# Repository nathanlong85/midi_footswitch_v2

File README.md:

# MIDI Footswitch v2

## The General Idea

The idea behind this is to be a customizable, solid footswitch for sending and receiving MIDI commands via USB. The following buttons will be implemented:

| Button | Count | Function |
|--------|-------|----------|
| MIDI PC  | 5 | Send a Program Change MIDI command to switch between presets, snapshots, etc. |
| MIDI CC  | 6 | Send a Control Change MIDI command to switch pedals on/off |
| PC StepDown | 1 | Lower the range of PC numbers corresponding with the buttons (e.g. 6-10 to 1-5) |
| PC StepUp | 1 | Raise the range of PC numbers corresponding with the buttons (e.g. 1-5 to 6-10) |
| TempoTap | 1 | This'll probably just end up being a CC button |

The main purpose of this footswitch is to control guitar plugins and presets, specifically in LiveProfessor, but the MIDI out features should all still work fine in another program. Additionally, the footswitch accepts MIDI input. This allows LiveProfessor to send (for example) CC commands when switching presets that will control the button states and have them match up with the plugin states in the preset.

For example, if I switch to a preset that has only a TS808 plugin enabled, the footswitch will first switch all CC buttons off. Then LiveProfessor can send a CC command back to the footswitch to let it know that the button that corresponds with the TS808 should be on.

## Components Used

| Type | Count | Brand | Model | Link | Notes |
|------|-------|-------|------|-------|-------|
| Arduino | 1 | Elegoo | Mega2560 | | Chosen for the large number of pins available for buttons |
| Connections Board | 1 | Custom | N/A | N/A | Mostly a convenience to make things as modular as possible. Also used in place of a breadboard for components such as resistors for the LEDs and switches |
| Display | 1 | Teyleten Robot | 2.42" 128x64 SSD1309 OLED | https://a.co/d/j11dIGv | Connected via SPI |
| LED | 14 | N/A | N/A | N/A | Red 5mm |
| LED Holder | 14 | DaierTek | 5MM LED Lamp Holder | https://a.co/d/9saOy9M | |
| SD Card Module | 1 | HiLetgo | Micro SD TF Card Adater Reader Module | https://a.co/d/amf9kn3 | Connected via SPI |
| SD Card | 1 | | | | No need for a high capacity as the only things being stored are configs |
| FootSwitch | 14 | ESUPPORT | Momentary SPST Button | https://a.co/d/4z8qo4Z | |
| TSR Jack | 1 | Kingsing | N/A | https://a.co/d/iaOluce | For the expression pedal |
| Switch | 1 | uxcell | SS12F32-G7 | https://a.co/d/9ZpxkgF | Mini slider switch to change USB modes from Midi to Arduino for uploads |
| USB Jack | 1 | QIANRENON | N/A | https://a.co/d/0RwaqkX | USB-A to USB-C converter and passthrough plate |

Additionally, various electrical components, connector wires, header pins, etc. were used. Those should be available in the KiCad schematics.

## Arduino Pin Assignments

| Number | Purpose | Notes |
|--------|---------|-------|
| 2 | SD Card SPI - CS | Ran out of pins to use near the other SPI pins |
| 22-26 | MIDI PC Button LEDs | Bottom row: buttons 1-5 |
| 27 | StepDown Button LED | Bottom row: button 6 |
| 28 | StepUp Button LED | Bottom row: button 7 |
| 29 | TempoTap Button LED | Bottom row: button 8 |
| 30-35 | MIDI CC Button LEDs | Top row: buttons 1-6 |
| 36-40 | MIDI PC Button Switches | Bottom row: buttons 1-5 |
| 41 | StepDown Button Switch | Bottom row: button 6 |
| 42 | StepUp Button Switch | Bottom row: button 7 |
| 43 | TempoTap Button Switch | Bottom row: button 8 |
| 44-49 | MIDI CC Button Switches | Top row: buttons 1-6 |
| 50 | SPI - MISO | Dictated by Arduino board |
| 51 | SPI - MOSI | Dictated by Arduino board |
| 52 | SPI - SCK | Dictated by Arduino board |
| 53 | Display SPI - CS | Conventional pin for first SPI device |

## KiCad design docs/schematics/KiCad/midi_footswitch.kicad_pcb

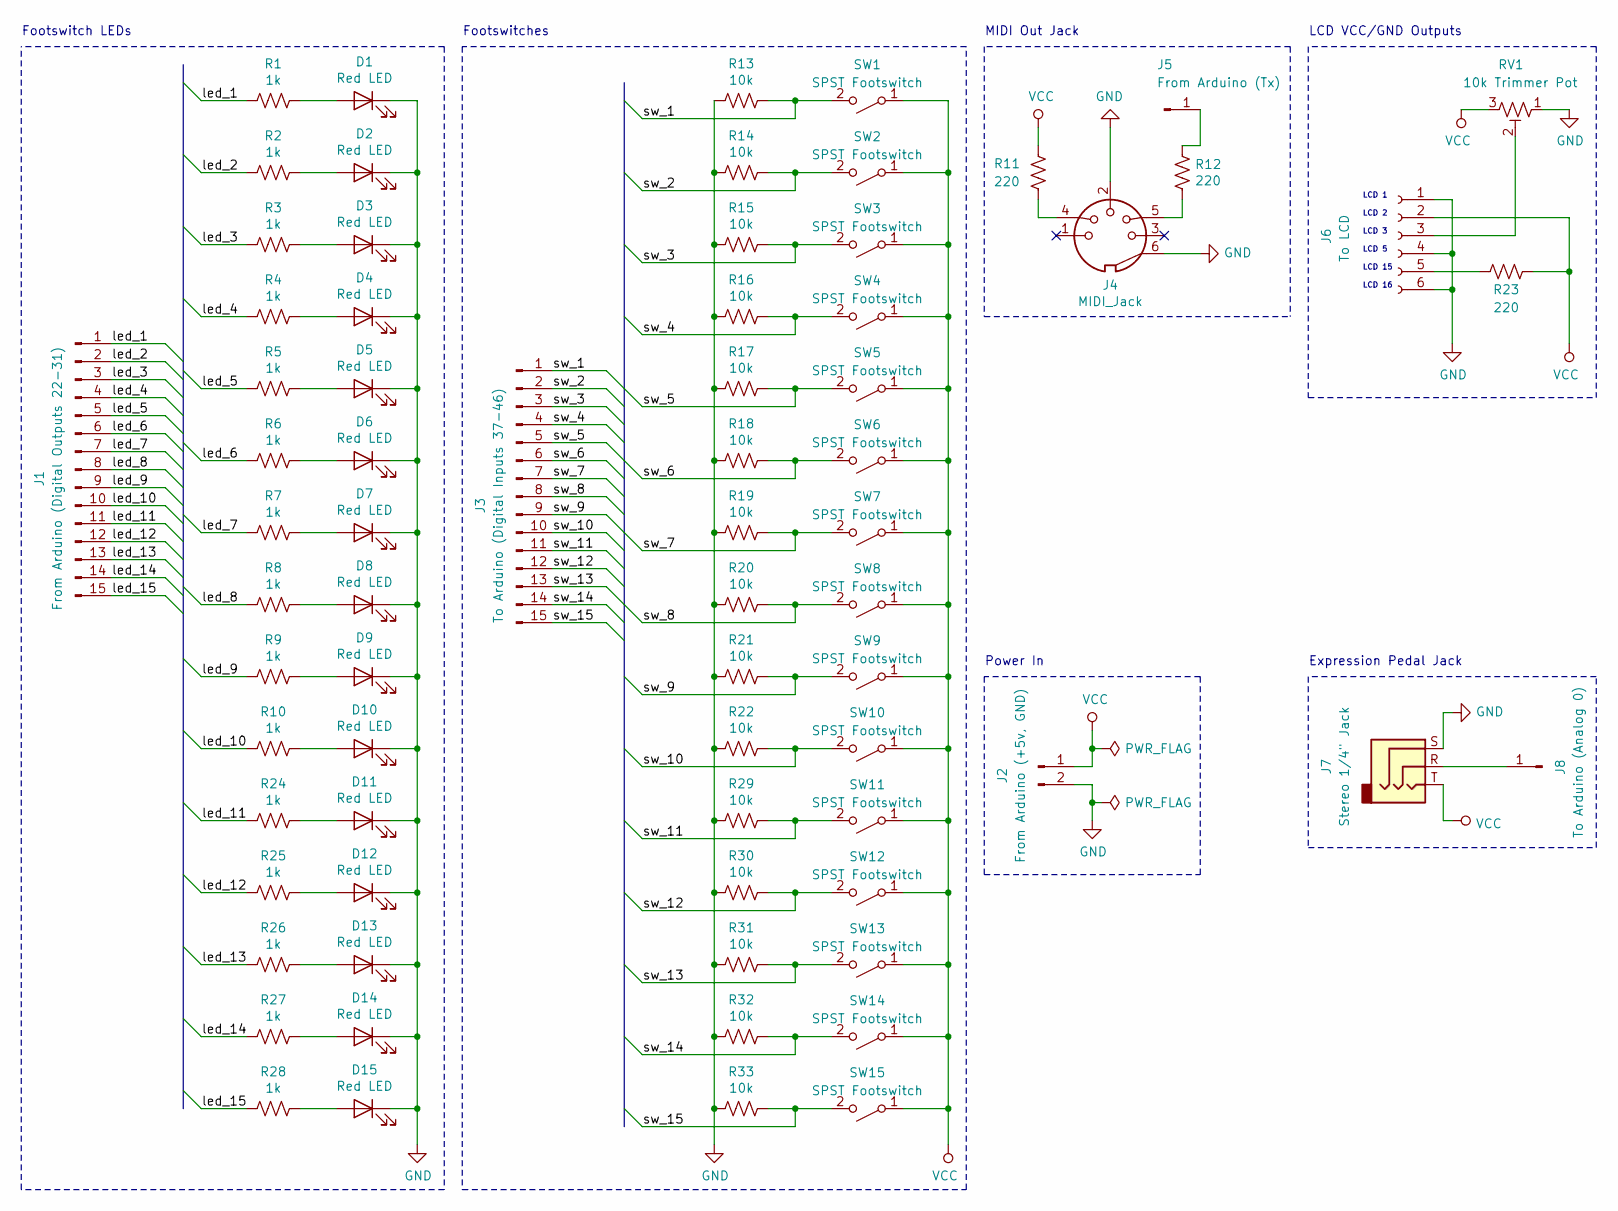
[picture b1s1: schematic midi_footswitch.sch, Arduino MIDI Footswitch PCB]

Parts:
D1, D2, D3, D4, D5, D6, D7, D8, D9, D10, D11, D12, D13, D14, D15: Red LED; LED_D5.0mm
J1: From Arduino (Digital Outputs 22-31); PinHeader_1x15_P2.54mm_Vertical
J2: From Arduino (+5v, GND); PinHeader_1x02_P2.54mm_Vertical
J3: To Arduino (Digital Inputs 37-46); PinHeader_1x15_P2.54mm_Vertical
J4: MIDI_Jack; midi_jack
J5: From Arduino (Tx); PinHeader_1x01_P2.54mm_Vertical
J6: To LCD; PinHeader_1x06_P2.54mm_Vertical
J7: Stereo 1/4\" Jack; audio_jack_stereo_quarter_inch
J8: To Arduino (Analog 0); PinHeader_1x01_P2.54mm_Vertical
R1, R2, R3, R4, R5, R6, R7, R8, R9, R10, R24, R25, R26, R27, R28: 1k; R_Axial_DIN0207_L6.3mm_D2.5mm_P10.16mm_Horizontal
R11, R12, R23: 220; R_Axial_DIN0207_L6.3mm_D2.5mm_P10.16mm_Horizontal
R13, R14, R15, R16, R17, R18, R19, R20, R21, R22, R29, R30, R31, R32, R33: 10k; R_Axial_DIN0207_L6.3mm_D2.5mm_P10.16mm_Horizontal
RV1: 10k Trimmer Pot; Potentiometer_Runtron_RM-065_Vertical
SW1, SW2, SW3, SW4, SW5, SW6, SW7, SW8, SW9, SW10, SW11, SW12, SW13, SW14, SW15: SPST Footswitch; spst_footswitch

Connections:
/led_1: J1.1, R1.2
/led_2: J1.2, R2.2
/led_3: J1.3, R3.2
/led_4: J1.4, R4.2
/led_5: J1.5, R5.2
/led_6: J1.6, R6.2
/led_7: J1.7, R7.2
/led_8: J1.8, R8.2
/led_9: J1.9, R9.2
/led_10: J1.10, R10.2
/led_11: J1.11, R24.2
/led_12: J1.12, R25.2
/led_13: J1.13, R26.2
/led_14: J1.14, R27.2
/led_15: J1.15, R28.2
/sw_1: J3.1, R13.1, SW1.2 (B)
/sw_2: J3.2, R14.1, SW2.2 (B)
/sw_3: J3.3, R15.1, SW3.2 (B)
/sw_4: J3.4, R16.1, SW4.2 (B)
/sw_5: J3.5, R17.1, SW5.2 (B)
/sw_6: J3.6, R18.1, SW6.2 (B)
/sw_7: J3.7, R19.1, SW7.2 (B)
/sw_8: J3.8, R20.1, SW8.2 (B)
/sw_9: J3.9, R21.1, SW9.2 (B)
/sw_10: J3.10, R22.1, SW10.2 (B)
/sw_11: J3.11, R29.1, SW11.2 (B)
/sw_12: J3.12, R30.1, SW12.2 (B)
/sw_13: J3.13, R31.1, SW13.2 (B)
/sw_14: J3.14, R32.1, SW14.2 (B)
/sw_15: J3.15, R33.1, SW15.2 (B)
GND: D1.1 (K), D2.1 (K), D3.1 (K), D4.1 (K), D5.1 (K), D6.1 (K), D7.1 (K), D8.1 (K), D9.1 (K), D10.1 (K), D11.1 (K), D12.1 (K), D13.1 (K), D14.1 (K), D15.1 (K), J2.2, J4.2, J4.6, J6.1, J6.4, J6.6, J7.S, R13.2, R14.2, R15.2, R16.2, R17.2, R18.2, R19.2, R20.2, R21.2, R22.2, R29.2, R30.2, R31.2, R32.2, R33.2, RV1.1
unnamed: D1.2 (A), R1.1
unnamed: D2.2 (A), R2.1
unnamed: D3.2 (A), R3.1
unnamed: D4.2 (A), R4.1
unnamed: D5.2 (A), R5.1
unnamed: D6.2 (A), R6.1
unnamed: D7.2 (A), R7.1
unnamed: D8.2 (A), R8.1
unnamed: D9.2 (A), R9.1
unnamed: D10.2 (A), R10.1
unnamed: D11.2 (A), R24.1
unnamed: D12.2 (A), R25.1
unnamed: D13.2 (A), R26.1
unnamed: D14.2 (A), R27.1
unnamed: D15.2 (A), R28.1
unnamed: J4.4, R11.2
unnamed: J4.5, R12.2
unnamed: J5.1, R12.1
unnamed: J6.3, RV1.2
unnamed: J6.5, R23.2
unnamed: J7.R, J8.1
VCC: J2.1, J6.2, J7.T, R11.1, R23.1, RV1.3, SW1.1 (A), SW2.1 (A), SW3.1 (A), SW4.1 (A), SW5.1 (A), SW6.1 (A), SW7.1 (A), SW8.1 (A), SW9.1 (A), SW10.1 (A), SW11.1 (A), SW12.1 (A), SW13.1 (A), SW14.1 (A), SW15.1 (A)

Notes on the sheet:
Footswitch LEDs
Footswitches
MIDI Out Jack
LCD VCC/GND Outputs
Power In
LCD 1
LCD 16
LCD 15
LCD 5
LCD 3
LCD 2
Expression Pedal Jack

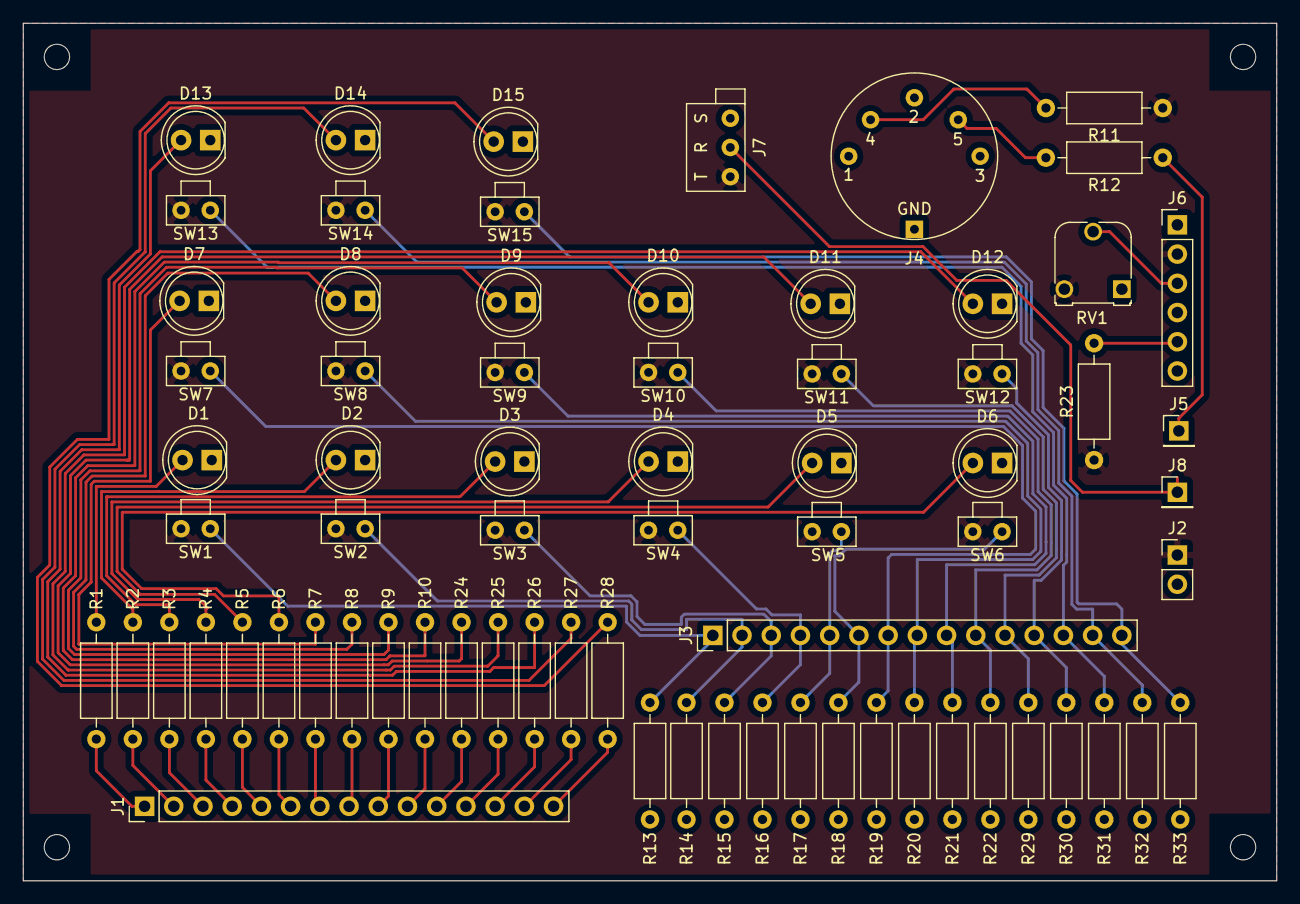
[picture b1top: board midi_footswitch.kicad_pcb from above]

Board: 2 copper layers, 109.0 x 74.5 mm, 72 parts (0 on the bottom side), 53 nets.

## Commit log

2022-11-07 Add initial code
2022-11-07 Add a readme
2022-11-07 Add .gitignore
2022-11-10 Clearing old files
2022-11-10 Add new files
2022-11-10 Code reorg
2022-11-11 More code reorganization
2022-11-17 Add more classes
2022-11-17 Add missing newlines
2022-11-22 Add CC buttons and features
2022-11-22 Small code analysis corrections
2022-11-22 Update variable initialization
2023-01-11 Add OLED, add CC logging
2023-01-11 Minor tweaks after testing on actual Arduino
2023-01-20 Added PC buttons
2023-01-26 Pushing PC step progress
